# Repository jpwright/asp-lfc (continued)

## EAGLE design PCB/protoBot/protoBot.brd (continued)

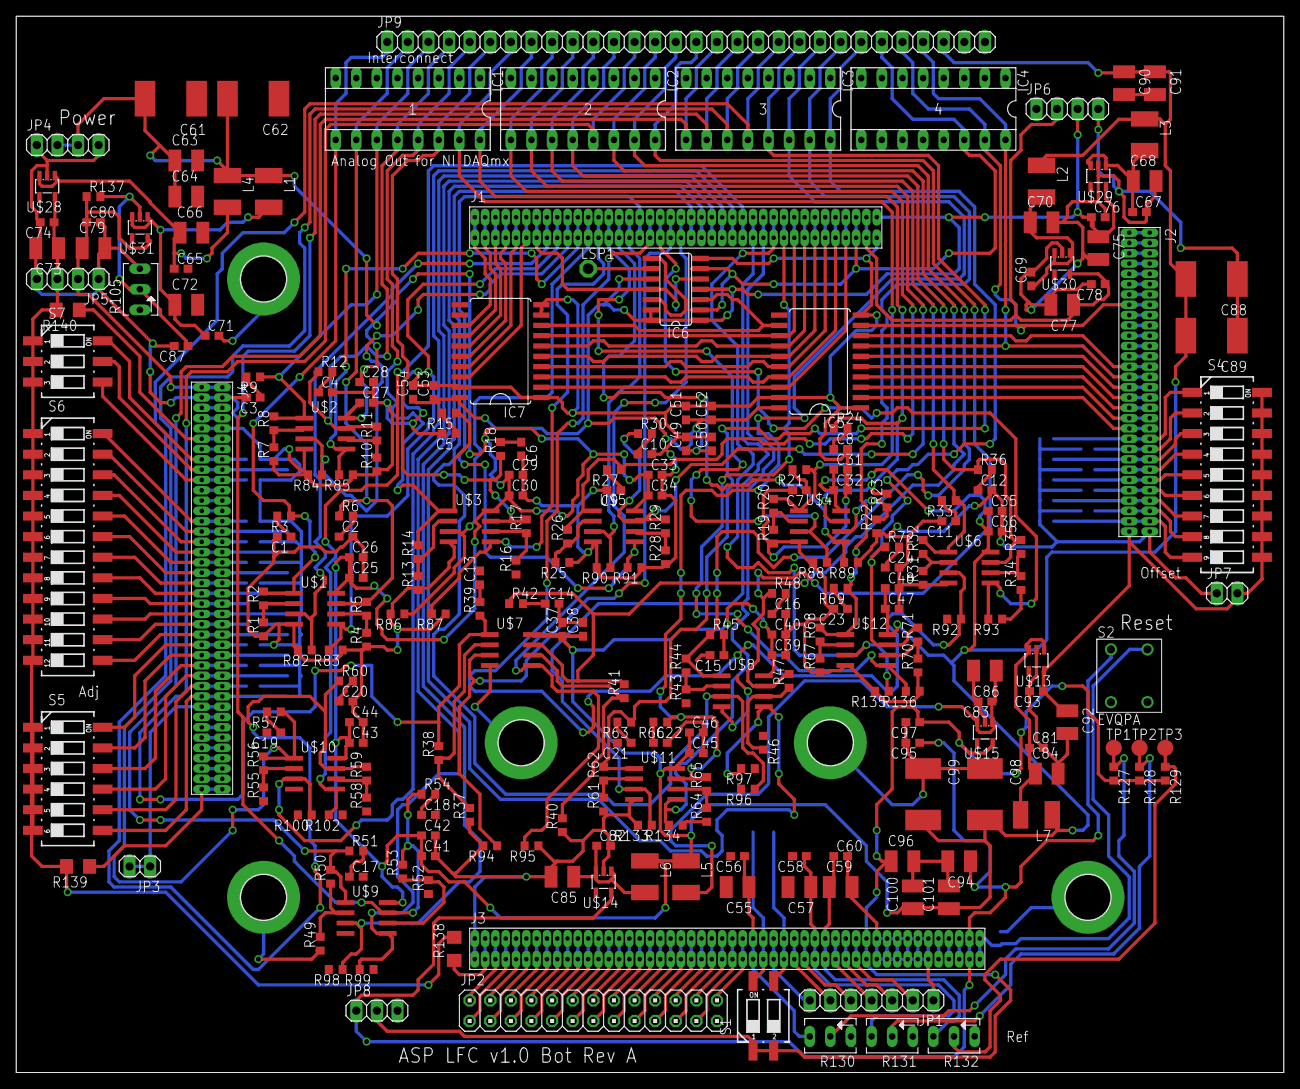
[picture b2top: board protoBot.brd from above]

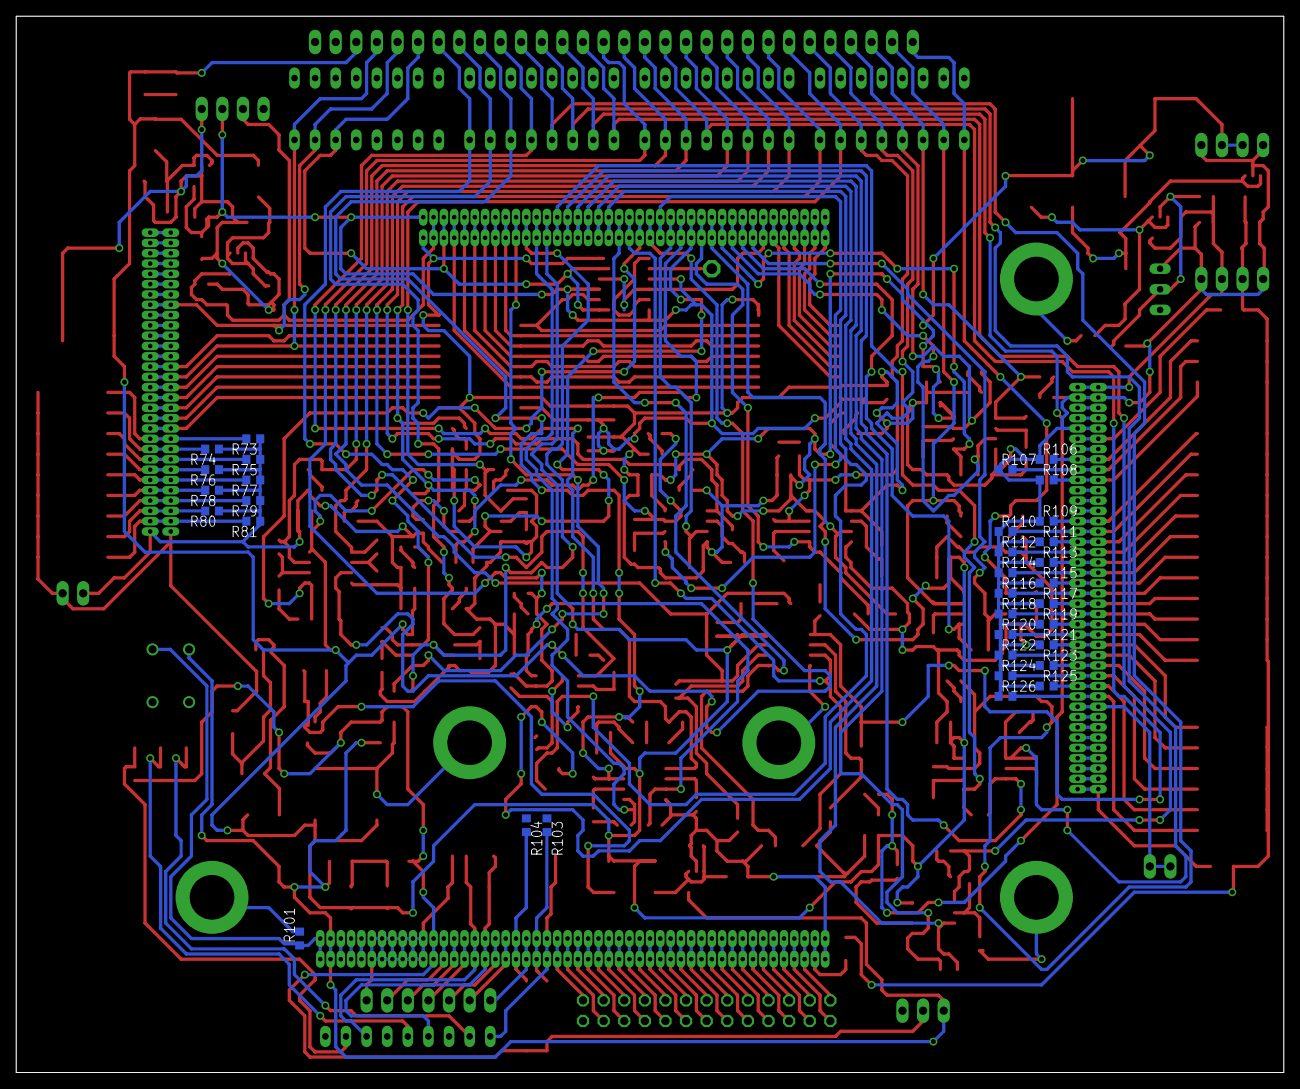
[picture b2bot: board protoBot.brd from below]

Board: 2 copper layers, 156.2 x 130.2 mm, 302 parts (33 on the bottom side), 239 nets.

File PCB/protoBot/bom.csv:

"Qty";"Value";"Device";"Package";"Parts";"Description";"";
"72";"";"C-USC0603";"C0603";"C1, C2, C3, C4, C5, C6, C7, C8, C9, C10, C11, C12, C13, C14, C15, C16, C17, C18, C19, C20, C21, C22, C23, C24, C25, C26, C27, C28, C29, C30, C31, C32, C33, C34, C35, C36, C37, C38, C39, C40, C41, C42, C43, C44, C45, C46, C47, C48, C49, C50, C51, C52, C53, C54, C56, C58, C60, C65, C67, C69, C71, C74, C76, C78, C80, C81, C82, C83, C87, C93, C95, C97";"CAPACITOR, American symbol";"";
"23";"";"C-USC1210";"C1210";"C55, C57, C59, C63, C64, C66, C68, C70, C72, C73, C75, C77, C79, C84, C85, C86, C90, C91, C92, C94, C96, C100, C101";"CAPACITOR, American symbol";"";
"6";"";"CPOL-USE/7260-38R";"E/7260-38R";"C61, C62, C88, C89, C98, C99";"POLARIZED CAPACITOR, American symbol";"";
"4";"";"DIL16S";"SOCKET-16";"IC1, IC2, IC3, IC4";"Dual In Line / Socket";"";
"7";"";"L-USL1812";"L1812";"L1, L2, L3, L4, L5, L6, L7";"INDUCTOR, American symbol";"";
"2";"";"PINHD-1X2";"1X02";"JP3, JP7";"PIN HEADER";"";
"1";"";"PINHD-1X3";"1X03";"JP8";"PIN HEADER";"";
"1";"";"PINHD-1X30";"1X30";"JP9";"PIN HEADER";"";
"3";"";"PINHD-1X4";"1X04";"JP4, JP5, JP6";"PIN HEADER";"";
"1";"";"PINHD-1X7";"1X07";"JP1";"PIN HEADER";"";
"1";"";"PINHD-2X13";"2X13";"JP2";"PIN HEADER";"";
"53";"";"R-US_R0603";"R0603";"R3, R6, R9, R12, R15, R18, R21, R24, R27, R30, R33, R36, R39, R42, R45, R48, R51, R54, R57, R60, R63, R66, R69, R72, R75, R76, R77, R78, R79, R80, R81, R104, R106, R107, R108, R109, R110, R111, R112, R113, R114, R115, R116, R117, R118, R119, R120, R121, R122, R123, R124, R125, R126";"RESISTOR, American symbol";"";
"4";"";"TRIM_US-B64Y";"B64Y";"R105, R130, R131, R132";"POTENTIOMETER";"";
"28";"10K";"R-US_R0603";"R0603";"R1, R4, R7, R10, R13, R16, R19, R22, R25, R28, R31, R34, R37, R40, R43, R46, R49, R52, R55, R58, R61, R64, R67, R70, R73, R74, R101, R103";"RESISTOR, American symbol";"";
"3";"10k";"R-US_R0603";"R0603";"R127, R128, R129";"RESISTOR, American symbol";"";
"24";"110K";"R-US_R0603";"R0603";"R82, R83, R84, R85, R86, R87, R88, R89, R90, R91, R92, R93, R94, R95, R96, R97, R98, R99, R100, R102, R133, R134, R135, R136";"RESISTOR, American symbol";"";
"1";"1k";"R-US_R0603";"R0603";"R137";"RESISTOR, American symbol";"";
"24";"20K";"R-US_R0603";"R0603";"R2, R5, R8, R11, R14, R17, R20, R23, R26, R29, R32, R35, R38, R41, R44, R47, R50, R53, R56, R59, R62, R65, R68, R71";"RESISTOR, American symbol";"";
"1";"219-02";"219-02";"CTS-219-02";"S1";"Surface Mount DIP Switch Series 219 SMT";"";
"1";"219-03";"219-03";"CTS-219-03";"S7";"Surface Mount DIP Switch Series 219 SMT";"";
"1";"219-06";"219-06";"CTS-219-06";"S5";"Surface Mount DIP Switch Series 219 SMT";"";
"1";"219-09";"219-09";"CTS-219-09";"S4";"Surface Mount DIP Switch Series 219 SMT";"";
"1";"219-12";"219-12";"CTS-219-12";"S6";"Surface Mount DIP Switch Series 219 SMT";"";
"2";"74LS540DW";"74LS540DW";"SO20W";"IC5, IC7";"Octal BUFFER and LINE DRIVER, 3-state";"";
"1";"74LS74D";"74LS74D";"SO14";"IC6";"Dual D type positive edge triggered FLIP FLOP, preset and clear";"";
"12";"AD823";"AD823";"SOIC-8";"U$1, U$2, U$3, U$4, U$5, U$6, U$7, U$8, U$9, U$10, U$11, U$12";"";"";
"7";"ADP151";"ADP151";"TSOT23-5";"U$13, U$14, U$15, U$28, U$29, U$30, U$31";"";"";
"1";"AMPMODU50-100";"AMPMODU50-100";"AMPMODU50-100";"J3";"";"";
"1";"AMPMODU50-60";"AMPMODU50-60";"AMPMODU50-60";"J2";"";"";
"2";"AMPMODU50-80";"AMPMODU50-80";"AMPMODU50-80";"J1, J4";"";"";
"1";"EVQPA";"EVQPA";"EVQPA";"S2";"Panasonic EVQPA tactile switch, 6.0mm x 6.0mm";"";
"5";"MOUNT-PAD-ROUND5.5";"MOUNT-PAD-ROUND5.5";"5,5-PAD";"H1, H2, H3, H4, H5";"MOUNTING PAD, round";"";
"1";"TPSPAD1-13";"TPSPAD1-13";"P1-13";"LSP1";"TEST PIN";"";
"3";"TPTP20R";"TPTP20R";"TP20R";"TP1, TP2, TP3";"Test pad";"";
"3";"open";"R-US_R1206";"R1206";"R138, R139, R140";"RESISTOR, American symbol";"";

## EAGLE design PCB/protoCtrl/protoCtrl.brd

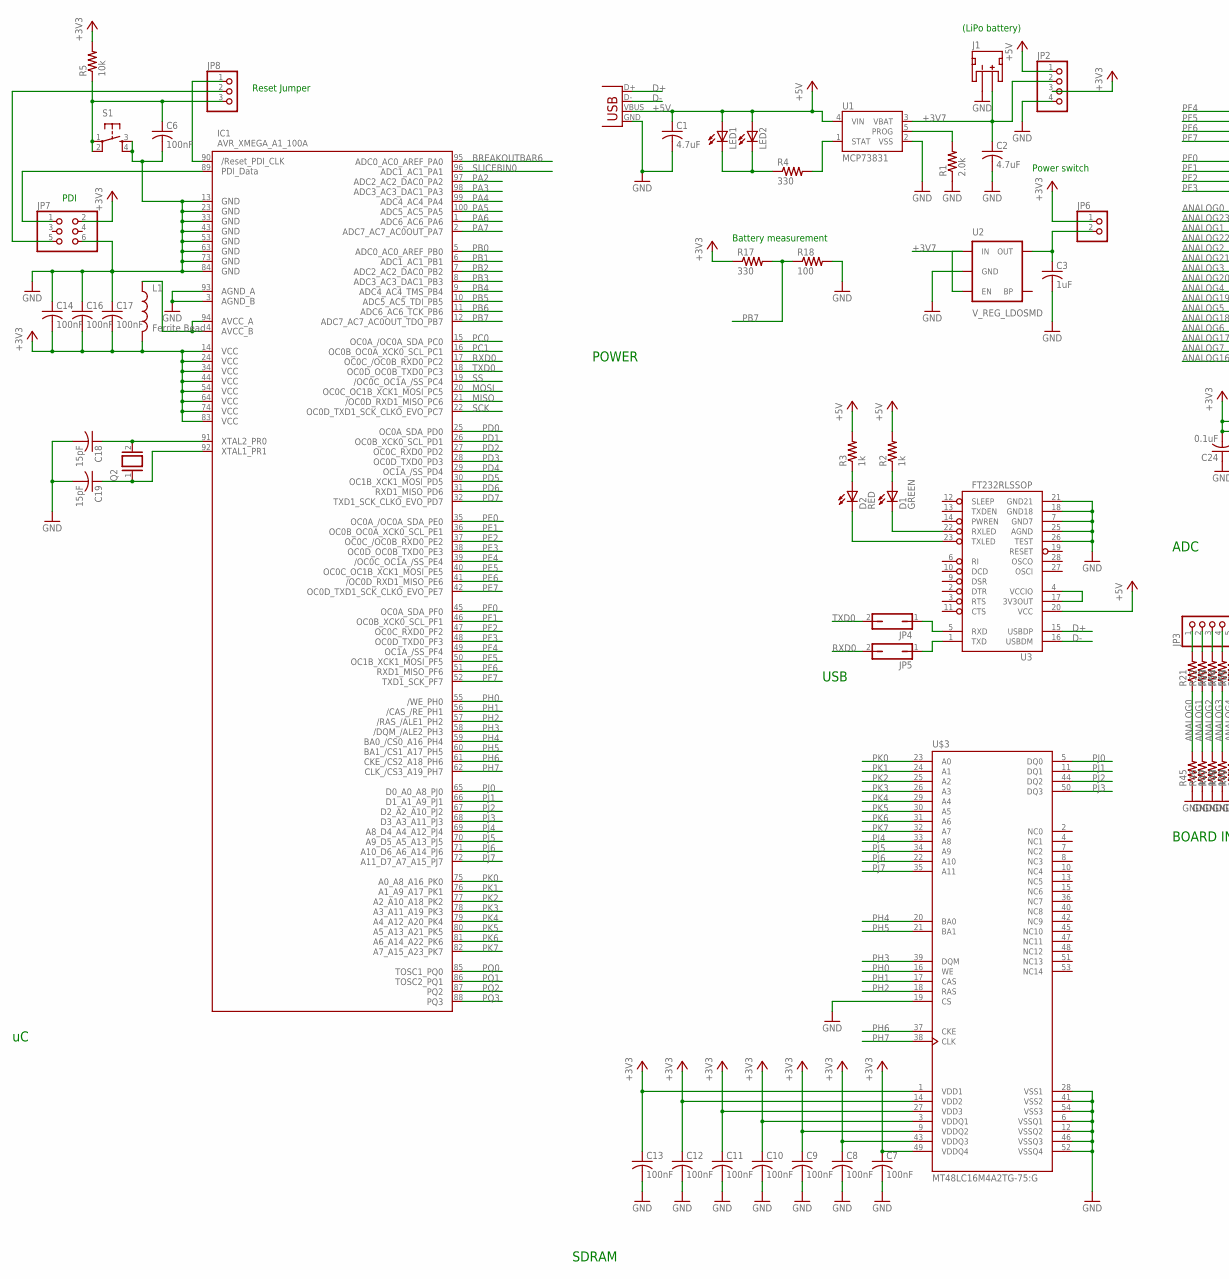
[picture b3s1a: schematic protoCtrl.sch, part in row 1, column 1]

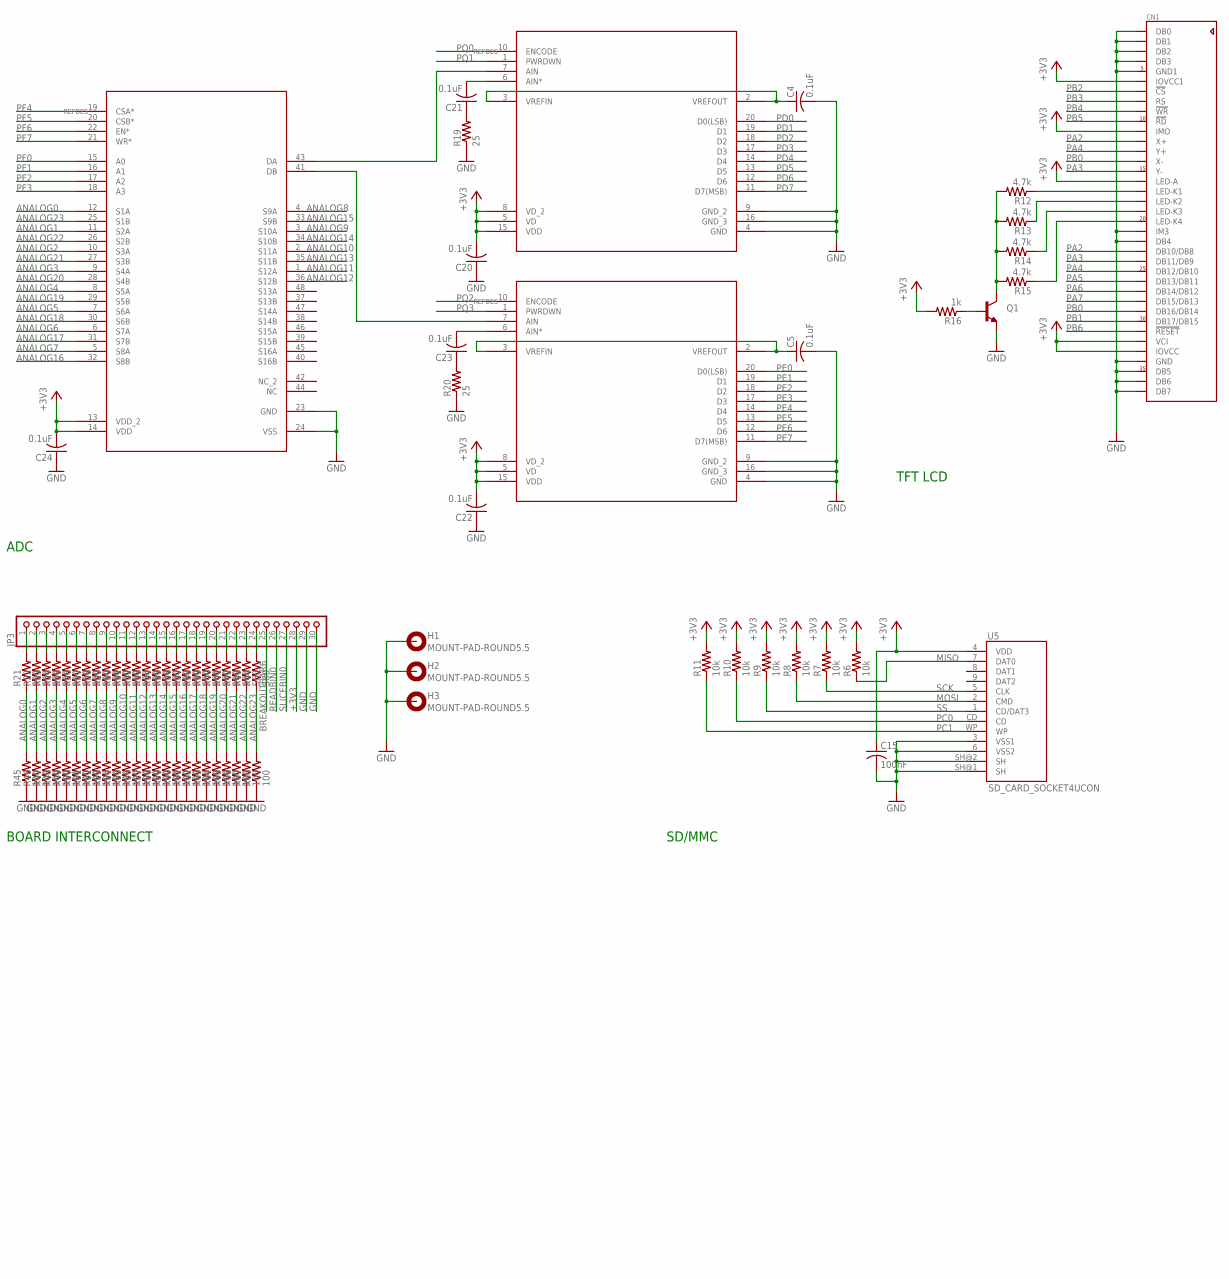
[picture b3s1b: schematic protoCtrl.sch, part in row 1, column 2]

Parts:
C1, C2: 4.7uF; C0603
C3: 1uF; C0603
C4, C5, C20, C21, C22, C23, C24: 0.1uF; C0603
C6, C7, C8, C9, C10, C11, C12, C13, C14, C15, C16, C17: 100nF; C0603
C18, C19: 15pF; C0603
CN1: ILI9325_LCD1.0MM; ILI9325_28INCH_TS
D1: GREEN; LED-0603
D2: RED; LED-0603
H1, H2, H3: MOUNT-PAD-ROUND5.5; 5,5-PAD
IC1: AVR_XMEGA_A1_100A; TQFP100
J1: JST_2MM_MALE; JST-2-SMD
JP1: USBSMD; USB-MINIB
JP2: PINHD-1X4; 1X04
JP3: PINHD-1X30; 1X30
JP4, JP5: JP1Q; JP1
JP6: PINHD-1X2; 1X02
JP7: PINHD-2X3; 2X03
JP8: PINHD-1X3; 1X03
L1: Ferrite Bead; 0603
LED1: LED1206; LED-1206
LED2: LED3MM
Q1: TRANSISTOR_NPN"; SOT223
Q2: XTAL/S; QS
R1: 2.0k; 0402-RES
R2, R3, R16: 1k; 0402-RES
R4, R17: 330; 0402-RES
R5, R6, R7, R8, R9, R10, R11: 10k; 0402-RES
R12, R13, R14, R15: 4.7k; 0402-RES
R18, R45, R46, R47, R48, R49, R50, R51, R52, R53, R54, R55, R56, R57, R58, R59, R60, R61, R62, R63, R64, R65, R66, R67, R68: 100; 0402-RES
R19, R20: 25; 0402-RES
R21, R22, R23, R24, R25, R26, R27, R28, R29, R30, R31, R32, R33, R34, R35, R36, R37, R38, R39, R40, R41, R42, R43, R44: 560; 0402-RES
S1: TAC_SWITCHPTH; TACTILE-PTH
U1: MCP73831; SOT23-5
U2: V_REG_LDOSMD; SOT23-5
U3: FT232RLSSOP; SSOP28DB
U4: ADG726BSUZ; SU_48
U5: SD_CARD_SOCKET4UCON; SDCARD_4UCONN
U6, U7: AD9283BRSZ-80REAL; SSOP20
U$3: MT48LC16M4A2TG-75:G; TSOP54-400

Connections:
+3V3: C7.1, C8.1, C9.1, C10.1, C11.1, C12.1, C13.1, C14.2, C15.1, C16.2, C17.2, C20.2, C22.2, C24.2, CN1.6 (IOVCC1), CN1.11 (IMO), CN1.16 (LED-A), CN1.32 (VCI), CN1.33 (IOVCC), IC1.14 (VCC1), IC1.24 (VCC2), IC1.34 (VCC3), IC1.44 (VCC4), IC1.54 (VCC5), IC1.64 (VCC6), IC1.74 (VCC7), IC1.83 (VCC8), JP2.3, JP3.28, JP6.1, JP7.2, L1.2, R5.2, R6.2, R7.2, R8.2, R9.2, R10.2, R11.2, R16.2, R17.1, U4.13 (VDD_2), U4.14 (VDD), U5.4 (VDD), U6.5 (VD), U6.8 (VD_2), U6.15 (VDD), U7.5 (VD), U7.8 (VD_2), U7.15 (VDD), U$3.1 (VDD1), U$3.3 (VDDQ1), U$3.9 (VDDQ2), U$3.14 (VDD2), U$3.27 (VDD3), U$3.43 (VDDQ3), U$3.49 (VDDQ4)
+3V7: C2.1, J1.2 (+), JP2.2, U1.3 (VBAT), U2.1 (IN), U2.3 (EN)
+5V: C1.1, JP1.VBUS, JP2.1, LED1.A, LED2.A, R2.2, R3.2, U1.4 (VIN), U3.20 (VCC)
ANALOG0: R21.1, R45.2, U4.12 (S1A)
ANALOG1: R22.1, R46.2, U4.11 (S2A)
ANALOG2: R23.1, R47.2, U4.10 (S3A)
ANALOG3: R24.1, R48.2, U4.9 (S4A)
ANALOG4: R25.1, R49.2, U4.8 (S5A)
ANALOG5: R26.1, R50.2, U4.7 (S6A)
ANALOG6: R27.1, R51.2, U4.6 (S7A)
ANALOG7: R28.1, R52.2, U4.5 (S8A)
ANALOG8: R29.1, R53.2, U4.4 (S9A)
ANALOG9: R30.1, R54.2, U4.3 (S10A)
ANALOG10: R31.1, R55.2, U4.2 (S11A)
ANALOG11: R32.1, R56.2, U4.1 (S12A)
ANALOG12: R33.1, R57.2, U4.36 (S12B)
ANALOG13: R34.1, R58.2, U4.35 (S11B)
ANALOG14: R35.1, R59.2, U4.34 (S10B)
ANALOG15: R36.1, R60.2, U4.33 (S9B)
ANALOG16: R37.1, R61.2, U4.32 (S8B)
ANALOG17: R38.1, R62.2, U4.31 (S7B)
ANALOG18: R39.1, R63.2, U4.30 (S6B)
ANALOG19: R40.1, R64.2, U4.29 (S5B)
ANALOG20: R41.1, R65.2, U4.28 (S4B)
ANALOG21: R42.1, R66.2, U4.27 (S3B)
ANALOG22: R43.1, R67.2, U4.26 (S2B)
ANALOG23: R44.1, R68.2, U4.25 (S1B)
BREAKOUTBAR6: IC1.95 (PA0), JP3.25
D+: JP1.D+, U3.15 (USBDP)
D-: JP1.D-, U3.16 (USBDM)
GND: C1.2, C2.2, C3.2, C4.2, C5.2, C6.2, C7.2, C8.2, C9.2, C10.2, C11.2, C12.2, C13.2, C14.1, C15.2, C16.1, C17.1, C18.2, C19.2, C20.1, C22.1, C24.1, CN1.1 (DB0), CN1.2 (DB1), CN1.3 (DB2), CN1.4 (DB3), CN1.5 (GND1), CN1.21 (IM3), CN1.22 (DB4), CN1.34 (GND), CN1.35 (DB5), CN1.36 (DB6), CN1.37 (DB7), H1.B5,5, H2.B5,5, H3.B5,5, IC1.3 (AGND_B), IC1.13 (GND1), IC1.23 (GND2), IC1.33 (GND3), IC1.43 (GND4), IC1.53 (GND5), IC1.63 (GND6), IC1.73 (GND7), IC1.84 (GND8), IC1.93 (AGND_A), J1.1 (-), JP1.GND, JP2.4, JP3.29, JP3.30, JP7.6, Q1.3 (E), R1.1, R18.2, R19.1, R20.1, R45.1, R46.1, R47.1, R48.1, R49.1, R50.1, R51.1, R52.1, R53.1, R54.1, R55.1, R56.1, R57.1, R58.1, R59.1, R60.1, R61.1, R62.1, R63.1, R64.1, R65.1, R66.1, R67.1, R68.1, S1.3, S1.4, U1.2 (VSS), U2.2 (GND), U3.7 (GND7), U3.18 (GND18), U3.21 (GND21), U3.25 (AGND), U3.26 (TEST), U4.23 (GND), U4.24 (VSS), U5.3 (VSS1), U5.6 (VSS2), U5.SH@1 (SH), U5.SH@2 (SH), U6.4 (GND), U6.9 (GND_2), U6.16 (GND_3), U7.4 (GND), U7.9 (GND_2), U7.16 (GND_3), U$3.6 (VSSQ1), U$3.12 (VSSQ2), U$3.19 (CS), U$3.28 (VSS1), U$3.41 (VSS2), U$3.46 (VSSQ3), U$3.52 (VSSQ4), U$3.54 (VSS3)
MISO: IC1.21 (PC6), R6.1, U5.7 (DAT0)
MOSI: IC1.20 (PC5), R8.1, U5.2 (CMD)
unnamed: D1.C, U3.22 (RXLED)
unnamed: LED1.C, LED2.K (C), R4.1
unnamed: D2.C, U3.23 (TXLED)
unnamed: R4.2, U1.1 (STAT)
unnamed: D2.A, R3.1
unnamed: R1.2, U1.5 (PROG)
unnamed: D1.A, R2.1
unnamed: JP5.1, U3.1 (TXD)
unnamed: U3.4 (VCCIO), U3.17 (3V3OUT)
unnamed: U4.43 (DA), U6.7 (AIN)
unnamed: U4.41 (DB), U7.7 (AIN)
unnamed: JP4.1, U3.5 (RXD)
unnamed: JP7.5, JP8.2
unnamed: C3.1, JP6.2, U2.5 (OUT)
unnamed: IC1.89 (PDI_DATA), JP7.1
unnamed: CN1.17 (LED-K1), R12.1
unnamed: CN1.18 (LED-K2), R13.1
unnamed: CN1.19 (LED-K3), R14.1
unnamed: CN1.20 (LED-K4), R15.1
unnamed: Q1.2 (C), R12.2, R13.2, R14.2, R15.2
unnamed: Q1.1 (B), R16.1
unnamed: IC1.4 (AVCC_B), IC1.94 (AVCC_A), L1.1
unnamed: IC1.90 (RESET), JP8.1
unnamed: C6.1, JP8.3, R5.1, S1.1, S1.2
unnamed: C18.1, IC1.91 (PR0), Q2.2
unnamed: C19.1, IC1.92 (PR1), Q2.1
unnamed: C4.1, U6.2 (VREFOUT), U6.3 (VREFIN)
unnamed: C21.1, R19.2
unnamed: C5.1, U7.2 (VREFOUT), U7.3 (VREFIN)
unnamed: C21.2, U6.6 (AIN*)
unnamed: C23.2, U7.6 (AIN*)
unnamed: C23.1, R20.2
unnamed: JP3.1, R21.2
unnamed: JP3.2, R22.2
unnamed: JP3.24, R44.2
unnamed: JP3.3, R23.2
unnamed: JP3.4, R24.2
unnamed: JP3.5, R25.2
unnamed: JP3.6, R26.2
unnamed: JP3.7, R27.2
unnamed: JP3.8, R28.2
unnamed: JP3.9, R29.2
unnamed: JP3.10, R30.2
unnamed: JP3.11, R31.2
unnamed: JP3.12, R32.2
unnamed: JP3.13, R33.2
unnamed: JP3.14, R34.2
unnamed: JP3.15, R35.2
unnamed: JP3.16, R36.2
unnamed: JP3.17, R37.2
unnamed: JP3.18, R38.2
unnamed: JP3.19, R39.2
unnamed: JP3.20, R40.2
unnamed: JP3.21, R41.2
unnamed: JP3.22, R42.2
unnamed: JP3.23, R43.2
PA2: CN1.12 (X+), CN1.23 (DB10/DB8), IC1.97 (PA2)
PA3: CN1.15 (Y-), CN1.24 (DB11/DB9), IC1.98 (PA3)
PA4: CN1.13 (Y+), CN1.25 (DB12/DB10), IC1.99 (PA4)
PA5: CN1.26 (DB13/DB11), IC1.100 (PA5)
PA6: CN1.27 (DB14/DB12), IC1.1 (PA6)
PA7: CN1.28 (DB15/DB13), IC1.2 (PA7)
PB0: CN1.14 (X-), CN1.29 (DB16/DB14), IC1.5 (PB0)
PB1: CN1.30 (DB17/DB15), IC1.6 (PB1)
PB2: CN1.7 (!CS), IC1.7 (PB2)
PB3: CN1.8 (RS), IC1.8 (PB3)
PB4: CN1.9 (!WR), IC1.9 (PB4)
PB5: CN1.10 (!RD), IC1.10 (PB5)
PB6: CN1.31 (!RESET), IC1.11 (PB6)
PB7: IC1.12 (PB7), R17.2, R18.1
PC0: IC1.15 (PC0), R10.1, U5.CD
PC1: IC1.16 (PC1), R11.1, U5.WP
PD0: IC1.25 (PD0), U6.20 (D0(LSB))
PD1: IC1.26 (PD1), U6.19 (D1)
PD2: IC1.27 (PD2), U6.18 (D2)
PD3: IC1.28 (PD3), U6.17 (D3)
PD4: IC1.29 (PD4), U6.14 (D4)
PD5: IC1.30 (PD5), U6.13 (D5)
PD6: IC1.31 (PD6), U6.12 (D6)
PD7: IC1.32 (PD7), U6.11 (D7(MSB))
PE0: IC1.35 (PE0), U7.20 (D0(LSB))
PE1: IC1.36 (PE1), U7.19 (D1)
PE2: IC1.37 (PE2), U7.18 (D2)
PE3: IC1.38 (PE3), U7.17 (D3)
PE4: IC1.39 (PE4), U7.14 (D4)
PE5: IC1.40 (PE5), U7.13 (D5)
PE6: IC1.41 (PE6), U7.12 (D6)
PE7: IC1.42 (PE7), U7.11 (D7(MSB))
PF0: IC1.45 (PF0), U4.15 (A0)
PF1: IC1.46 (PF1), U4.16 (A1)
PF2: IC1.47 (PF2), U4.17 (A2)
PF3: IC1.48 (PF3), U4.18 (A3)
PF4: IC1.49 (PF4), U4.19 (CSA*)
PF5: IC1.50 (PF5), U4.20 (CSB*)
PF6: IC1.51 (PF6), U4.22 (EN*)
PF7: IC1.52 (PF7), U4.21 (WR*)
PH0: IC1.55 (PH0), U$3.16 (WE)
PH1: IC1.56 (PH1), U$3.17 (CAS)
PH2: IC1.57 (PH2), U$3.18 (RAS)
PH3: IC1.58 (PH3), U$3.39 (DQM)
PH4: IC1.59 (PH4), U$3.20 (BA0)
PH5: IC1.60 (PH5), U$3.21 (BA1)
PH6: IC1.61 (PH6), U$3.37 (CKE)
PH7: IC1.62 (PH7), U$3.38 (CLK)
PJ0: IC1.65 (PJ0), U$3.5 (DQ0)
PJ1: IC1.66 (PJ1), U$3.11 (DQ1)
PJ2: IC1.67 (PJ2), U$3.44 (DQ2)
PJ3: IC1.68 (PJ3), U$3.50 (DQ3)
PJ4: IC1.69 (PJ4), U$3.33 (A8)
PJ5: IC1.70 (PJ5), U$3.34 (A9)
PJ6: IC1.71 (PJ6), U$3.22 (A10)
PJ7: IC1.72 (PJ7), U$3.35 (A11)
PK0: IC1.75 (PK0), U$3.23 (A0)
PK1: IC1.76 (PK1), U$3.24 (A1)
PK2: IC1.77 (PK2), U$3.25 (A2)
PK3: IC1.78 (PK3), U$3.26 (A3)
PK4: IC1.79 (PK4), U$3.29 (A4)
PK5: IC1.80 (PK5), U$3.30 (A5)
PK6: IC1.81 (PK6), U$3.31 (A6)
PK7: IC1.82 (PK7), U$3.32 (A7)
PQ0: IC1.85 (PQ0), U6.10 (ENCODE)
PQ1: IC1.86 (PQ1), U6.1 (PWRDWN)
PQ2: IC1.87 (PQ2), U7.10 (ENCODE)
PQ3: IC1.88 (PQ3), U7.1 (PWRDWN)
READBIN0: JP3.26
RXD0: IC1.17 (PC2), JP5.2
SCK: IC1.22 (PC7), R7.1, U5.5 (CLK)
SLICEBIN0: IC1.96 (PA1), JP3.27
SS: IC1.19 (PC4), R9.1, U5.1 (CD/DAT3)
TXD0: IC1.18 (PC3), JP4.2

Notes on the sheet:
POWER
(LiPo battery)
USB
ADC
Power switch
PDI
SDRAM
SD/MMC
Reset Jumper
Battery measurement
TFT LCD
BOARD INTERCONNECT

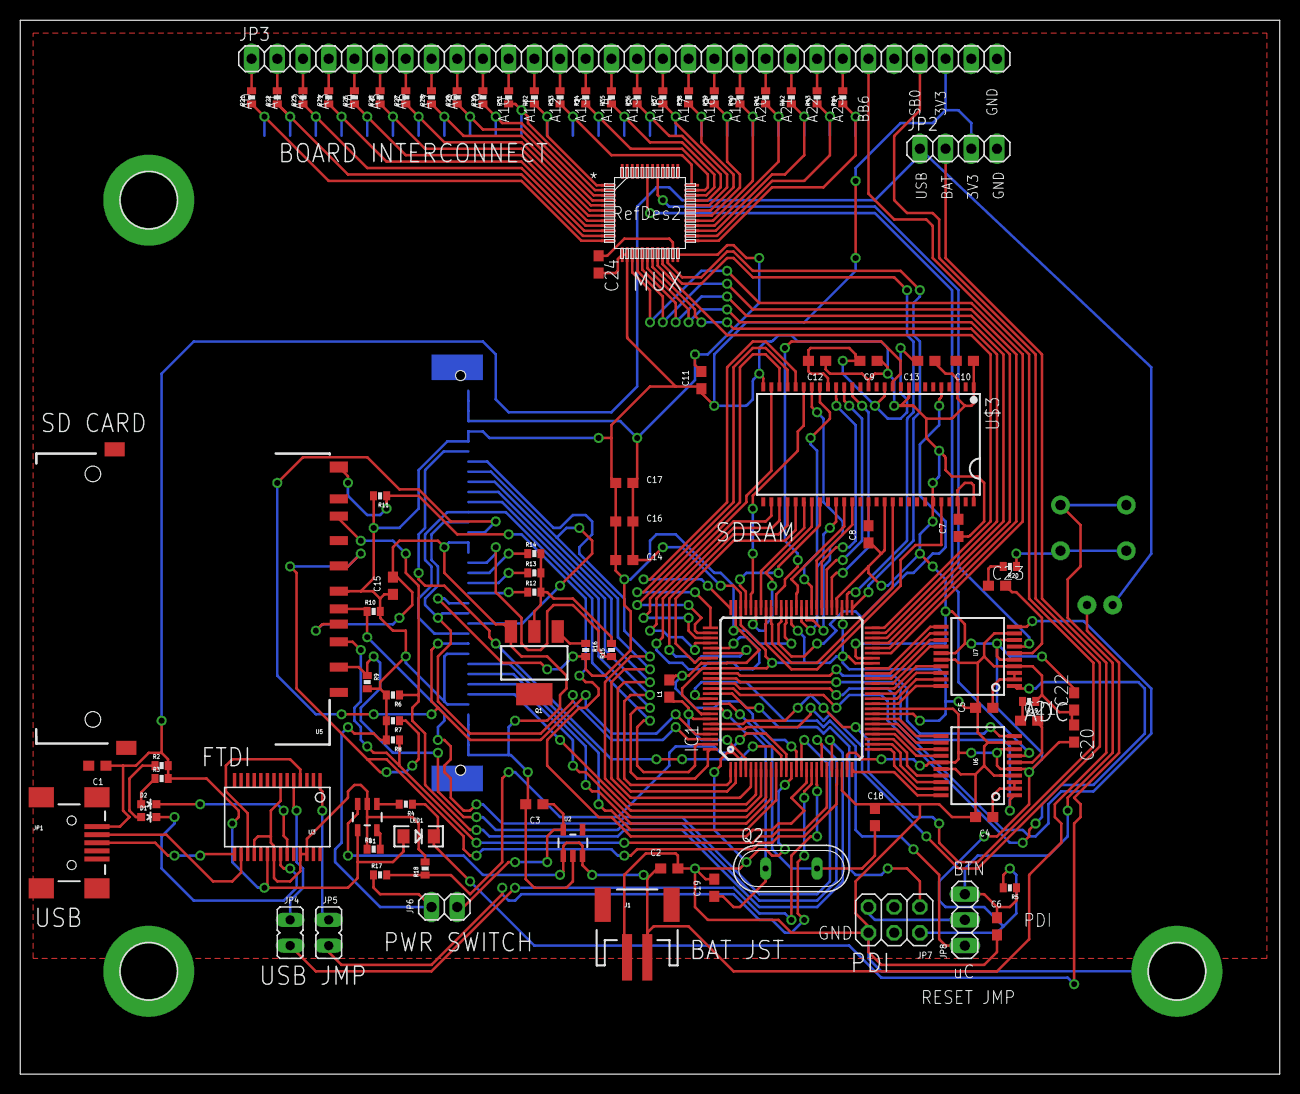
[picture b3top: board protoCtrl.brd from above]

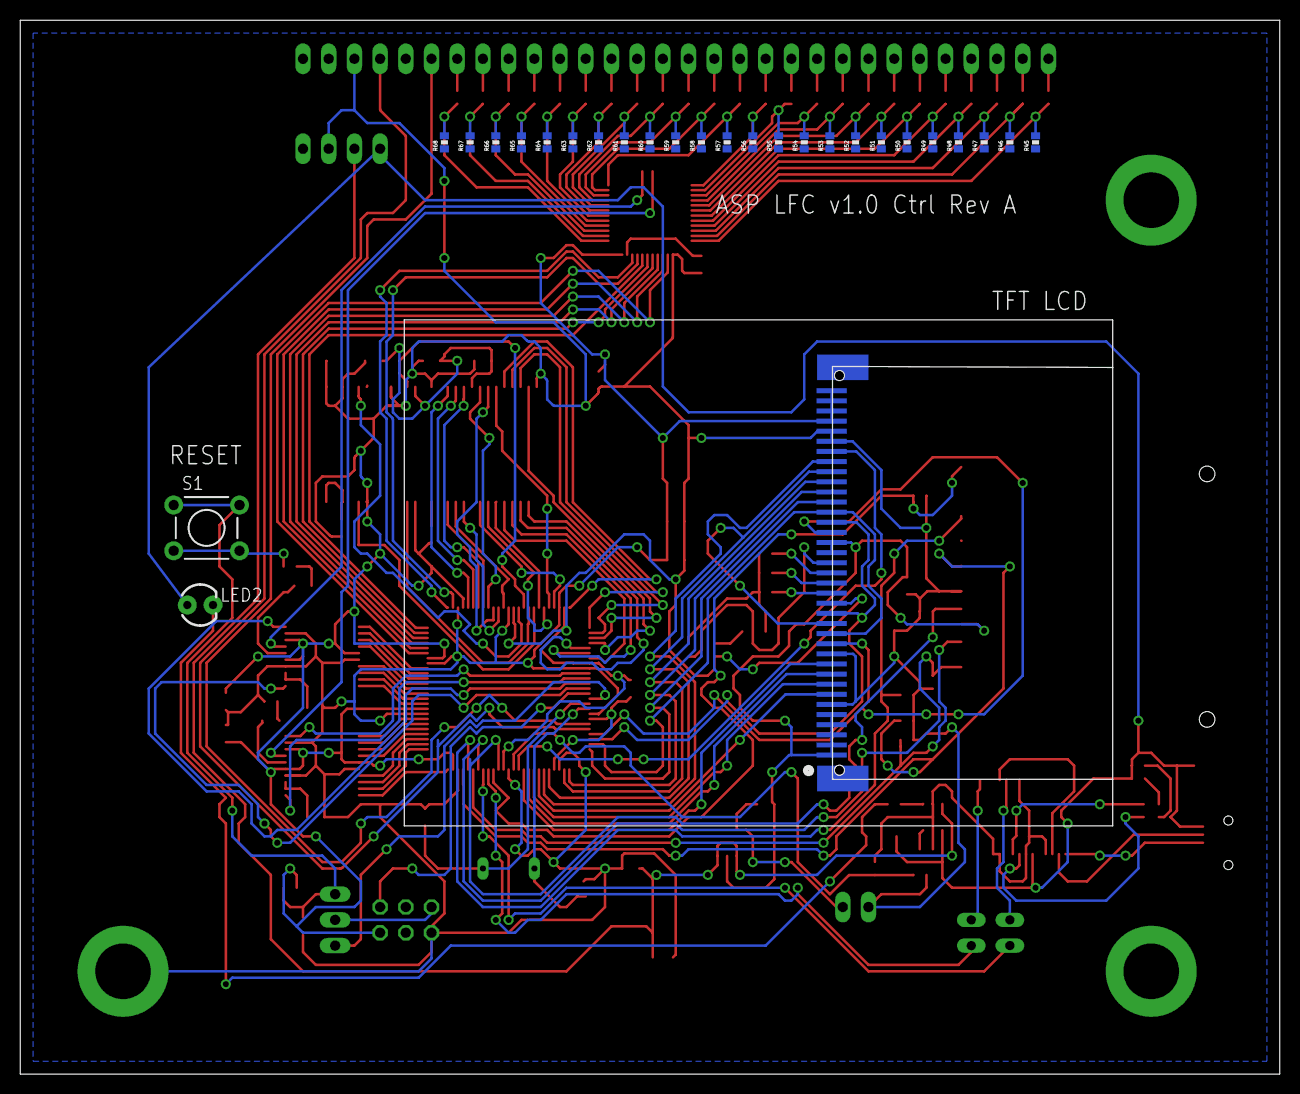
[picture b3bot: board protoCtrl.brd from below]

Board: 2 copper layers, 124.5 x 104.1 mm, 122 parts (27 on the bottom side), 162 nets.

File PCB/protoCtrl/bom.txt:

Partlist exported from C:/SPB_Data/eagle/protoCtrl/protoCtrl.sch at 1/11/2013 2:42:51 PM

Part Value             Device               Package     Description                                                                             PROD_ID    VALUE
C1   4.7uF             C-USC0603            C0603       CAPACITOR, American symbol                                                                              
C2   4.7uF             C-USC0603            C0603       CAPACITOR, American symbol                                                                              
C3   1uF               C-USC0603            C0603       CAPACITOR, American symbol                                                                              
C4   0.1uF             C-USC0603            C0603       CAPACITOR, American symbol                                                                              
C5   0.1uF             C-USC0603            C0603       CAPACITOR, American symbol                                                                              
C6   100nF             C-USC0603            C0603       CAPACITOR, American symbol                                                                              
D1   GREEN             LED-GREEN0603        LED-0603    Various green LEDs                                                                      DIO-00821  GREEN
D2   RED               LED-RED0603          LED-0603    Assorted Red LEDs                                                                       DIO-00819  RED  
IC1  AVR_XMEGA_A1_100A AVR_XMEGA_A1_100A    TQFP100     Device for Atmel AVR XMEGA A1 Series                                                                    
J1                     JST_2MM_MALE         JST-2-SMD   Mates to single-cell LiPo batteries.                                                    CONN-08352      
JP1  USBSMD            USBSMD               USB-MINIB   USB Connectors                                                                                          
JP2                    PINHD-1X4            1X04        PIN HEADER                                                                                              
JP3                    PINHD-1X30           1X30        PIN HEADER                                                                                              
JP4                    JP1Q                 JP1         JUMPER                                                                                                  
JP5                    JP1Q                 JP1         JUMPER                                                                                                  
JP6                    PINHD-1X2            1X02        PIN HEADER                                                                                              
JP7                    PINHD-2X3            2X03        PIN HEADER                                                                                              
LED1                   LED1206              LED-1206    LEDs                                                                                                    
LED2                   LED3MM               LED3MM      LEDs                                                                                                    
R1   2.0k              2.0KOHM1/10W5%(0603) 0402-RES    RES-08296                                                                               RES-08296  2.0k 
R2   1k                1K-1%                0402-RES    1k-ohm SMT                                                                              RES-07856  1k   
R3   1k                1K-1%                0402-RES    1k-ohm SMT                                                                              RES-07856  1k   
R4   330               330OHM1/10W1%(0603)  0402-RES    RES-00818                                                                               RES-00818  330  
R5   10k               2.0KOHM1/10W5%(0603) 0402-RES    RES-08296                                                                               RES-08296  2.0k 
S1                     TAC_SWITCHPTH        TACTILE-PTH Momentary Switch                                                                                        
U$1  AD9283            AD9283               RS-20                                                                                                               
U$2  AD9283            AD9283               RS-20                                                                                                               
U1   MCP73831          MCP73831             SOT23-5     Miniature single cell, fully integrated Li-Ion, Li-polymer charge management controller IC-09995        
U2   V_REG_LDOSMD      V_REG_LDOSMD         SOT23-5     Voltage Regulator LDO                                                                                   
U3   FT232RLSSOP       FT232RLSSOP          SSOP28DB    USB UART                                                                                IC-00870        
U4   ADG726BSUZ        ADG726BSUZ           SU_48

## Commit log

2013-05-15 PCB commit
2013-05-15 AVR commit
2013-05-15 MATLAB commit
2013-05-15 3D commit
2013-05-15 NI commit
2013-05-15 added ADC calculation script
2013-05-15 cleaning up ASP-LFC.c
2013-05-17 updated SDRAM.c to include steps to recreate issue
2013-06-01 adding images and cleaning up
